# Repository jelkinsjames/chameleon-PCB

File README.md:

# University of Washington Engine Chameleon Team 2023
This repo documents the University of Washington ENGINE 2023 Chameleon Team's journey towards creating a digital, modular synthesizer - a **Chameleon**. The team consists of Todd Bloom, Max Chastain, Nathan Ford, Julian James, and Trina Kha. The mentor for the project is Eric Klavins.

Each individual component of the project has its own README.md file. The instructional files are:
- [PCM1863 ADC](https://github.com/jelkinsjames/chameleon-PCB/tree/main/PCM1863/README.md)
- [PCM5242 DAC](https://github.com/jelkinsjames/chameleon-PCB/blob/main/PCM5242/README.md)

Eric Klavins hosts GitHub repos with the software used for the project. The software is Yet Another Synthesizer Engine (YASE). Links to relevant repos are provided below:
- [yase](https://github.com/klavins/yase.git): The synthesizer engine used in the project.
- [yase-template](https://github.com/klavins/yase-template.git): The template .makefile to be used when installing YASE.
- [potato-recipies](https://github.com/klavins/potato-recipies.git): Instructions on how to install and use YASE on Le Potato (an alternate board similar to a Raspberry Pi).
- [arty-z7-20-recipies](https://github.com/klavins/arty-z7-20-recipes.git): Instructions on how to install and use YASE on an ARTY-Z7-20 (an alternate board similar to a Raspberry Pi).

## Project Overview:

The Chameleon can function as a waveform generator, filter, effect, sequencer, and any other programmable module.

The **user interface** includes: *four LEDs, four rotary encoders, and four toggle switches.*

The **inputs** are: *Two stereo S/PDIF inputs* to take incoming data from other Chameleons and *two line-level mono-analog audio inputs.*

The **outputs** are: *Four stereo S/PDIF outputs* (carrying the same signal) that can be connected to other Chameleons and *two line-level mono-analog audio outputs.*

---

## Block Diagram:

### ARTY-Z7:
- [Xilinx Zynq 7020 SoC Processor](https://digilent.com/shop/arty-z7-zynq-7000-soc-development-board/)
- 650 MHz Dual core ARM processor
- 85,000 cell FPGA
- [Xilinx I2S FPGA module](https://www.xilinx.com/products/intellectual-property/audio-i2s.html)
- Four stereo channels that can be input or output
- 24-bit data at a frequency to be determined
- We are not sure if two I2S modules can be implemented. If so, we can have more I/O

The Chameleon Module sits on top of the ARTY board, which has female pin headers in the shape of an Arduino shield.

### Digital Inputs and Outputs (I/O):
- Each S/PDIF signal is stereo
- Inter-Chameleon connections are stereo
- You can’t split them into two mono signals from separate Chameleons.
- Digital I/O is managed by multiple DIX4192s
- Although there are four DINs, only one can be used at a time.
- There are two I2S lines, both can be either input or output

### Analog Inputs and Outputs (I/O):
- Analog input is managed by a [PCM1863 ADC](https://www.ti.com/product/PCM1863)
- Analog output is managed by a [PCM5242 DAC](https://www.ti.com/product/PCM5242)

### Front Panel and Skins:
- Front panel is black PCB with holes for UI elements
- PCB silkscreen is used for graphics
- The front panel fits in standard [Euroracks](https://en.wikipedia.org/wiki/Eurorack)
- Laser cut "skins" can be swapped out to match current Chameleon functionality

---

## User Interface (U/I):
- The UI is managed by an [ATSAMD21](https://www.microchip.com/en-us/product/ATsamd21g18) microcontroller
- The UI has four rotary encoders, LEDs, and toggle switches
- A custom I2C protocol is used to: *query the state of encoders and switches, reset encoders, and set LEDs.*

**The I2C Protocol is Register Based:**
- Each LED and switch correspond to a single bit in a single-byte-sized register
- Each encoder has a reset bit in a half-byte-sized reset register. Setting the corresponding bit high will reset the encoder's position
- Each encoder has a position register that can be read. When read, the register gives the position of the encoder in the range [0,255].

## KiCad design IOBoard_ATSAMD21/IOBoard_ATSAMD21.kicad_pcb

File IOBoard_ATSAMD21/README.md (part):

# I/O Board - ATSAMD21G18-A

---

This repository contains the hardware and software components of the I/O board for the Chameleon project.
The goal for this portion of the project is to create a peripheral to control [YASE](https://github.com/klavins/YASE). It can interface with any CPU using the I2C bus, and will allow users to modify parameters in YASE. The I/O board has rotary encoders, switches, and LEDs that the user can configure using I2C commands.

---
- [Hardware](#Hardware)

  - [Rotary Encoders](#Rotary-Encoders)
  - [Microcontrollers](#Microcontrollers)
  - [PCB Design](#PCB-Design)
  - [Analog Inputs and Outputs](#Analog-Inputs-and-Outputs)
  - [Programming/Debugging](#Programming-and-Debugging)

- [Software](#Software)
  - [Sercom I2C Functionality](#Sercom-I2C-Functionality)
  - [Talking to the IO Board](#Talking-to-the-IO-Board)

---
## Hardware

### Rotary Encoders
To allow users to modify YASE parameters with a knob, we are using rotary encoders. While rotary encoders may appear visually similar to a potentiometer you may find on a guitar or analog synthesizer module, they are fundamentally different. Instead of behaving like a variable resistor, rotary encoders are more similar to a rotary, dual-pole, dual-throw switch. Rotary encoders also spin indefinitely and do not have a start and end like a potentiometer.

The [How To Mechatronics](https://howtomechatronics.com/tutorials/arduino/rotary-encoder-works-use-arduino/) website has a great tutorial and explanation for how rotary encoders work.

A rotary encoder has 3 pins. The middle pin (C) is a shared power pin, which is connected to a power source. As the encoder spins, a brush powered by the middle pin makes contact with the left (A) and right (B) pins in sequence.

Since A and B are sent high at slightly different times, we can determine the direction of spin by measuring the state of A and B when a change in one is detected. This task is surprisingly simple to code.
Initially, we sample the value of `A` as value `aLast`. In a loop, we check to see if `aLast == A`. If `A != aLast`, we check the value of `B`. If `B == A`, we know `B` changed before `A` and the knob has been turned to the left. If `B != A`, then we know `A` changed first and the knob was turned to the right. Sample C code for managing one encoder is shown below.

```C
uint8_t encVal = 0;
_Bool aLast = A;
while(1) {
  if (A != aLast) {
    if(A != B) {
      encVal++;
    } else {
      encVal--;
    }
  }
  aLast = A;
}
```

I chose to use the PEC12R-3217F-S0024-ND rotary encoders because other similar projects used them. They include an extra switch that goes high when you press down on the knob. As an added bonus, they make a very satisfying clicking sound when pressed.

### Microcontrollers

The state of the encoders, LEDs, and switches are managed by a microprocessor. Initially I prototyped using the Arduino UNO, due its ease of use. However, the ATMEGA328P microcontroller it uses does not have enough GPIO to support the amount of peripherals we decided to use.

We have 4 rotary encoders, 4 switches, and 4 LEDs. Each encoder uses 3 GPIO (2 for the encoder and one for the pushbutton switch). Each switch and LED uses one GPIO. On top of this, I need two pins for accessing the I2C bus. This totals 22 GPIO. I could have used two microcontrollers, however choosing one that has enough GPIO to begin with seemed like a smarter idea so that I wouldn't have to write two separate programs.

This GPIO requirement led me to the ATSAMD21G18, an ARM-based microcontroller used on the Arduino Zero. This microprocessor is honestly way more powerful than we will take advantage of, but they are relatively cheap, widely available, and have more than enough GPIO. This will allow expansion in the future if a different team decides they want to add something else!

### PCB Design

The biggest design consideration made for the PCB was making it compatible with other Eurorack modules. Eurorack modules have the following size constraints:
- Height - 128.5mm/5.06"
- Width - in increments of 0.2", called a Horizontal Pitch (HP)
- Mounting holes - 3.2mm diameter
- Left mounting holes aligned 3mm from top and bottom edge, and 7.45mm from the left edge
- Right mounting holes aligned in HP increments from the left holes

For the IO board, I chose a width of 15HP. I found this size to be a good width for fitting all the components we needed. Since the I/O board will be sitting underneath the front panel, I reduced the overall dimension by 16.5mm. This allows the board to fit nicely inside a Eurorack style skiff.

I placed the rotary encoders, LEDs, and switches on a grid of 0.1" so that I could make them symmetrical across the middle of the board. I used a smaller grid for the ATSAMD21G18 and bypass capacitors to make routing easier. The ATSAMD21G18 has both internal pull up and pull down resistors, so there was no need to include extra resistors on the board, except for the resistors used for the LEDs. I found 10k ohms to yield a good brightness for the LEDs in testing.

For power, I am using a 3.3v LDO. I chose this instead of stealing power from the main computer in hopes that it may be a little more stable and allow for expansion in the future.

Next to every power pin on the SAMD21, I included two bypass capacitors. I chose 0.1uF and 10uF capacitors as it is typically recommended the larger bypass capacitor are 100x the smaller's capacitance. Ideally, I would have used both a tantalum and a ceramic capacitor for better performance, but as this board is purely digital I am not overly concerned with noise. Ceramic capacitors are not polar, so it is a little easier to assemble the boards using both ceramic.

All capacitors and resistors use the 0603 package for consistency.

The entire back copper layer of my PCB is a ground plane. This makes it very easy to ground anything that I need by placing a via. Once all of my components were connected to the ATSAMD21G18, I made the rest of the front copper layer a +3.3v power plane. This meant I did not have to route any power traces on the board, vastly simplifying the amount of time it took to design the PCB.

The switches are single throw, dual pole. This choice was made largely because they are much cheaper than single throw, single pole switches and readily available. I connected the middle pin to power, and the top pin to the SAM's GPIO.

### Analog Inputs and Outputs

In the final version of this board, I added 6 mono-analog jacks to the bottom half of the board. The left four are inputs, designed to go to the ADC. There are dedicated switches to choose which of the inputs you are using. The leftmost two are for control voltage (CV) and the middle two are for line level (LL). CV typically ranges from 0-10V, while LL ranges from 0-1V. Because of these vastly different voltage ranges, these inputs are buffered using an op-amp to prevent damage to the ADC board. The two rightmost jacks are dedicated to DAC out. These include an op-amp pre-amplification stage for lower signal-to-noise ratio.

The DAC output and ADC input pins are located on the rear of the I/O board, and are designed to be connected to the DAC and ADC peripherals designed by my teammates.

**These inputs will do nothing without an ADC or DAC. They do not interface with the D21.**

### Programming and Debugging

I use the Microchip PICkit4 to debug/program the SAMD21. I used the recommended debug header provided by KiCad 6. While this seemed to be easy initially, I realized that there was no easily accessible documentation as to what the PICkit4's 8 pins do! Different resources were saying different things, so it required a little guess and check work. To make matters worse, for some silly reason pin 1 of the PICkit4 is the furthest **RIGHT** instead of furthest left like every other convention you might be used to. The only clue I had to this was the arrow pointing at that pin.

To make things much easier for you, here is a list of the PICkit4 pins and where to plug them into the IO Board (from right to left)

1. MCLR
2. VDD
3. GND
4. Not connected
5. SWCLK
6. Not connected  
7. Not connected
8. SWDIO

The recommended header I used on my PCB has this in the same order and are labeled clearly, this should be very straight forward. Once plugged into the powered board, MPLAB will automatically recognize that it has a valid device to program. You may need to select the PICkit4 as your debugger in the IDE somewhere if this does not work automatically.

---

## Software

Programming the ATSAMD21G18 is fairly straight forward (with a few exceptions mostly due to Microchip's bad documentation). I am using the PICkit4 debugger to program the SAM. To write the code, I initially thought I may be able to use the Arduino IDE. This which would vastly simplify the programming, and may still be possible. The Arduino IDE supports the SAMD21, however it does not have support for the PICkit4. It supports the Atmel ICE debugger, which no longer exists since Microchip bought Atmel and now uses the PICkit4 as it's preferred debugger even though the ATSAM family of chips were originally produced by Atmel. *Can you tell I'm annoyed about this?*

I'm sure it is possible to trick the Arduino IDE into thinking that the PICkit4 is an Atmel ICE, but I do not know how to do that.

Instead, I am using Microchip's [MPLAB X IDE](https://www.microchip.com/mplab) to program my SAMD21. In true Microchip fashion, this turned out to be way more work than I wanted it to be! My goal was to use the Harmony3 tool to assist with configuring the chip. This is supposed to be installed by default, but for some reason it was not.

I had to clone the [GitHub repository for the MPLAB Harmony Content Manager](https://github.com/Microchip-MPLAB-Harmony/contentmanager), run it from the terminal, and use that to install the required packages for Harmony3. Once all of that was finished, I was finally able to use Harmony to write most of the code I needed. While this certainly saved me from reading the datasheet for hours and hours to learn how to program the chip, it led to the problem of me not understanding how the code worked at all!

### SERCOM I2C Functionality
My first big mistake was not enabling smart mode for the SERCOM I2C module inside Harmony3. Smart mode automates most of the I2C transactions, which greatly simplifies the coding. Before I realized that I should be using smart mode, I ran into a very strange issue with the address match interrupt. The code generate by Harmony3 included an interrupt manager. For whatever reason, the interrupt manager would not reset the address match interrupt and instead would get stuck in a time-out state. It took me weeks to figure out what was going on, and in the end it just took me turning smart mode on and Harmony rewrote the interrupt manager to deal with the issue I was having.

Once smart mode was enabled, all that is left to do is write a callback function for the SERCOM I2C module. Using a switch statement allows you to choose desired behavior when certain events take place. For my code, I only care about receiving and sending data, and do not care about doing anything specific on address match or on an error. A basic form of this callback function is shown below.

```C
uint8_t rxReg;
uint8_t txReg;
bool I2C_Callback(SERCOM_I2C_SLAVE_TRANSFER_EVENT event, uintptr_t contextHandle) {
    switch(event) {
      case SERCOM_I2C_SLAVE_TRANSFER_EVENT_RX_READY:
          rxReg = SERCOM0_I2C_ReadByte();
          // You can execute any code you want here, I use another switch statement
          switch(rxReg) {
            case 0x00:
              ENC0_val = 0;
              txReg = ENC0_val;
              break;

            case 0x01:
              txReg = ENC0_val;
              break;                
          }
        break;

      case SERCOM_I2C_SLAVE_TRANSFER_EVENT_TX_READY:
          SERCOM0_I2C_WriteByte(txReg);
          txReg = 0;
        break;
    }
    return true;
}
```

For this project, we will always read a value before writing a value. The value we write is determined by the value previously read. Because of this, I fill `txReg` with the correct data based on what we read from the I2C host. For example, if the host wishes to read the value of `ENC0`, it will first write `0x01` to `rxReg`. We next check the value of `rxReg` and enter the correct case statement. As shown above we just fill `txReg` with `ENC0_val`.

Once this host write operation has finished, the host will initiate a read operation. The I/O Board will respond with the contents of `txReg` and then reset the value to 0. My callback function always returns `true`. If you return false instead, the I2C acknowledgement bit will not be set high. This can be useful to tell the host that data is not ready for transmission. For my application there are no cases in which we won't send valid data, so I always return `true`.

The events you can add to your callback function are as follows:
- `SERCOM_I2C_SLAVE_TRANSFER_EVENT_RX_READY`
- `SERCOM_I2C_SLAVE_TRANSFER_EVENT_TX_READY`
- `SERCOM_I2C_SLAVE_TRANSFER_EVENT_ADDR_MATCH`
- `SERCOM_I2C_SLAVE_TRANSFER_EVENT_STOP_BIT_RECEIVED`
- `SERCOM_I2C_SLAVE_TRANSFER_EVENT_ERROR`

Now that we have a completed callback function, we just need to tell the SERCOM module to use this function by calling `SERCOM0_I2C_CallbackRegister(I2C_Callback, 0)` in our main function.

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
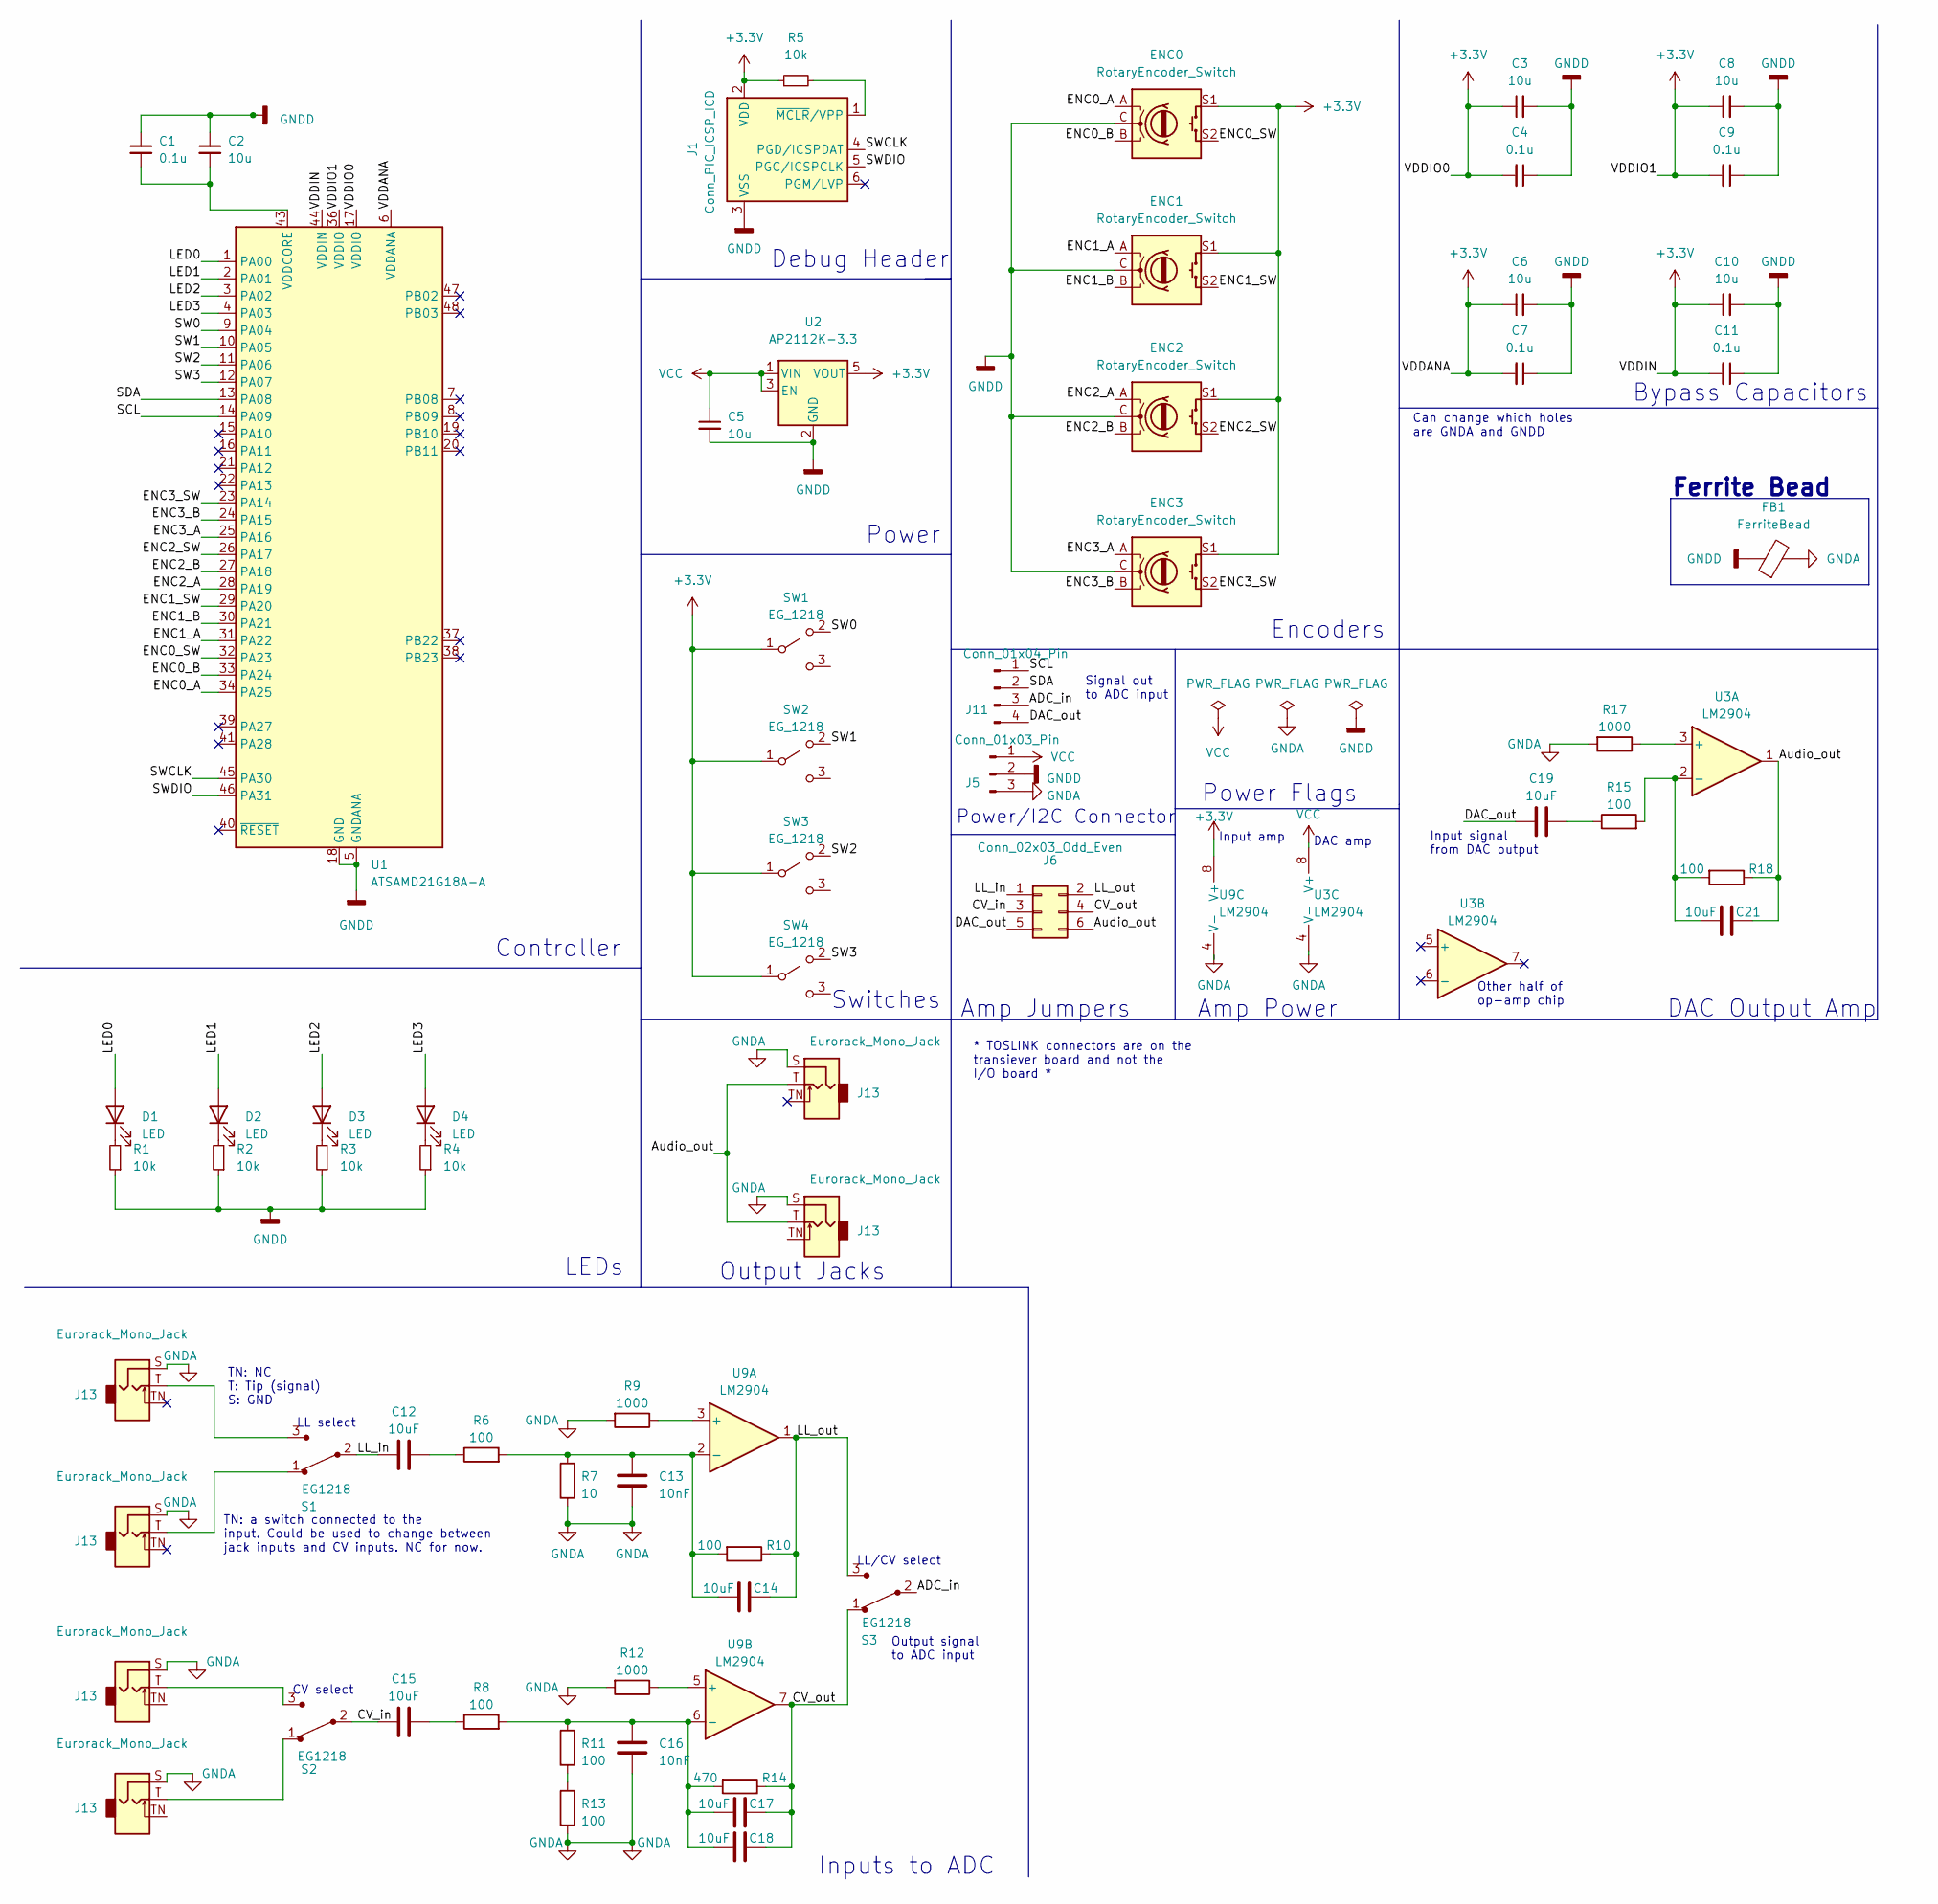
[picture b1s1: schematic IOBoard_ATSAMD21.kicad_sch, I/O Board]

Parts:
C1, C4, C7, C9, C11: 0.1u; C_0603_1608Metric
C2, C3, C5, C6, C8, C10: 10u; C_0603_1608Metric
C12, C14, C15, C17, C18, C19, C21: 10uF; C_0603_1608Metric
C13, C16: 10nF; C_0603_1608Metric
D1, D2, D3, D4: LED; LED_Rectangular_W5.0mm_H2.0mm
ENC0, ENC1, ENC2, ENC3: RotaryEncoder_Switch; PEC12R-3217F-S0024-ND
FB1: FerriteBead; L_0603_1608Metric_Pad1.05x0.95mm_HandSolder
J1: Conn_PIC_ICSP_ICD; PinHeader_1x06_P2.54mm_Vertical
J5: Conn_01x03_Pin; PinHeader_1x03_P2.54mm_Vertical
J6: Conn_02x03_Odd_Even; PinHeader_2x03_P2.54mm_Vertical
J11: Conn_01x04_Pin; PinHeader_1x04_P2.54mm_Vertical
J13: Eurorack_Mono_Jack; AudioJack_WQP518MA; MPN WQP-WQP518MA
R1, R2, R3, R4, R5: 10k; R_0603_1608Metric
R6, R8, R10, R11, R13, R15, R18: 100; R_0603_1608Metric
R7: 10; R_0603_1608Metric
R9, R12, R17: 1000; R_0603_1608Metric
R14: 470; R_0603_1608Metric
S1, S2, S3: EG1218; EG_1218; MPN EG1218; Digi-Key_PN EG1903-ND
SW1, SW2, SW3, SW4: EG_1218
U1: ATSAMD21G18A-A; TQFP-48_7x7mm_P0.5mm
U2: AP2112K-3.3; SOT-23-5
U3, U9: LM2904; SOIC-8_3.9x4.9mm_P1.27mm

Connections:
+3.3V: C3.1, C4.2, C6.1, C7.2, C8.1, C9.2, C10.1, C11.2, ENC0.S1, ENC1.S1, ENC2.S1, ENC3.S1, J1.2 (VDD), R5.1, SW1.1, SW2.1, SW3.1, SW4.1, U1.6 (VDDANA), U1.17 (VDDIO), U1.36 (VDDIO), U1.44 (VDDIN), U2.5 (VOUT), U9.8 (V+)
/ADC_in: J11.3, S3.2
/Audio_out: C21.1, J6.6, R18.1, U3.1; also elsewhere on the board
/CV_in: C15.1, J6.3, S2.2
/CV_out: C17.1, C18.1, J6.4, R14.1, S3.1, U9.7
/DAC_out: C19.1, J6.5, J11.4
/ENC0_A: ENC0.A, U1.34 (PA25)
/ENC0_B: ENC0.B, U1.33 (PA24)
/ENC0_SW: ENC0.S2, U1.32 (PA23)
/ENC1_A: ENC1.A, U1.31 (PA22)
/ENC1_B: ENC1.B, U1.30 (PA21)
/ENC1_SW: ENC1.S2, U1.29 (PA20)
/ENC2_A: ENC2.A, U1.28 (PA19)
/ENC2_B: ENC2.B, U1.27 (PA18)
/ENC2_SW: ENC2.S2, U1.26 (PA17)
/ENC3_A: ENC3.A, U1.25 (PA16)
/ENC3_B: ENC3.B, U1.24 (PA15)
/ENC3_SW: ENC3.S2, U1.23 (PA14)
/LED0: D1.2 (A), U1.1 (PA00)
/LED1: D2.2 (A), U1.2 (PA01)
/LED2: D3.2 (A), U1.3 (PA02)
/LED3: D4.2 (A), U1.4 (PA03)
/LL_in: C12.1, J6.1, S1.2
/LL_out: C14.1, J6.2, R10.1, S3.3, U9.1
/SCL: J11.1, U1.14 (PA09)
/SDA: J11.2, U1.13 (PA08)
/SW0: SW1.2, U1.9 (PA04)
/SW1: SW2.2, U1.10 (PA05)
/SW2: SW3.2, U1.11 (PA06)
/SW3: SW4.2, U1.12 (PA07)
/SWCLK: J1.4 (PGD/ICSPDAT), U1.45 (PA30)
/SWDIO: J1.5 (PGC/ICSPCLK), U1.46 (PA31)
GNDA: C13.1, C16.1, FB1.2, J5.3, R7.1, R9.2, R12.2, R13.1, R17.2, U3.4 (V-), U9.4 (V-); also elsewhere on the board
GNDD: C1.1, C2.1, C3.2, C4.1, C5.2, C6.2, C7.1, C8.2, C9.1, C10.2, C11.1, ENC0.C, ENC1.C, ENC2.C, ENC3.C, FB1.1, J1.3 (VSS), J5.2, R1.1, R2.1, R3.1, R4.1, U1.5 (GNDANA), U1.18 (GND), U1.35 (GND), U1.42 (GND), U2.2 (GND)
unnamed: C12.2, R6.1
unnamed: C15.2, R8.1
unnamed: C19.2, R15.1
unnamed: D1.1 (K), R1.2
unnamed: D2.1 (K), R2.2
unnamed: D3.1 (K), R3.2
unnamed: D4.1 (K), R4.2
unnamed: J1.1 (~MCLR/VPP), R5.2
unnamed 42: S1.3; also elsewhere on the board
unnamed 43: S1.1; also elsewhere on the board
unnamed 44: S2.3; also elsewhere on the board
unnamed 45: S2.1; also elsewhere on the board
unnamed: R11.1, R13.2
unnamed: C1.2, C2.2, U1.43 (VDDCORE)
unnamed: R17.1, U3.3 (+)
unnamed: C21.2, R15.2, R18.2, U3.2 (-)
unnamed: R9.1, U9.3 (+)
unnamed: C13.2, C14.2, R6.2, R7.2, R10.2, U9.2 (-)
unnamed: R12.1, U9.5 (+)
unnamed: C16.2, C17.2, C18.2, R8.2, R11.2, R14.2, U9.6 (-)
VCC: C5.1, J5.1, U2.1 (VIN), U2.3 (EN), U3.8 (V+)

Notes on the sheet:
LL/CV select
TN: NC T: Tip (signal) S: GND
Input signal from DAC output
Other half of op-amp chip
CV select
LEDs
DAC amp
DAC Output Amp
Debug Header
Encoders
Amp Jumpers
Output Jacks
Switches
Ferrite Bead
Power
Input amp
* TOSLINK connectors are on the transiever board and not the I/O board *
Amp Power
Inputs to ADC
Power/I2C Connector
Signal out to ADC input
TN: a switch connected to the input. Could be used to change between jack inputs and CV inputs. NC for now.
Controller
LL select
Bypass Capacitors
Can change which holes are GNDA and GNDD
Power Flags
Output signal to ADC input

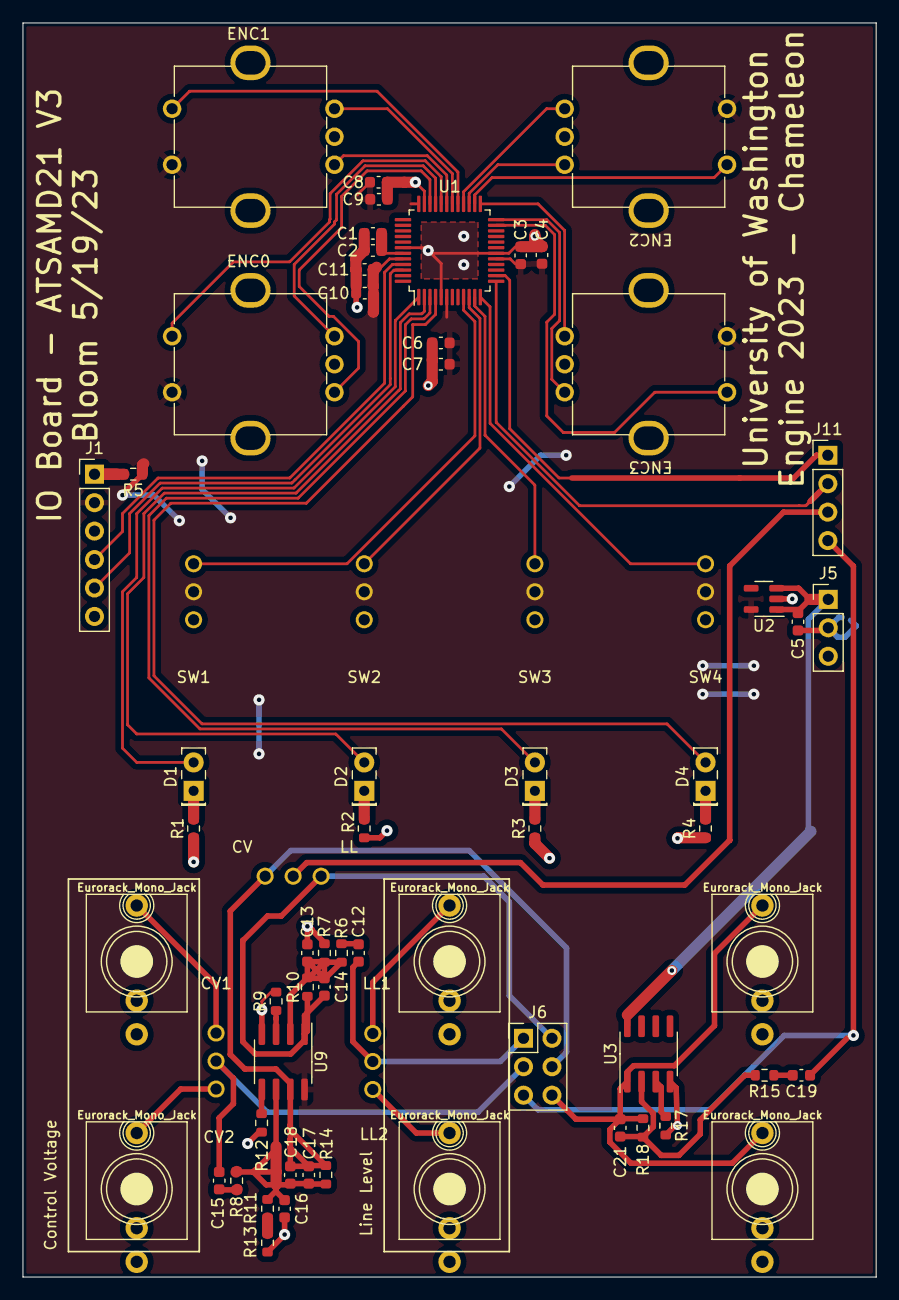
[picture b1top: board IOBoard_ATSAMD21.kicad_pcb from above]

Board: 2 copper layers, 76.2 x 112.0 mm, 67 parts (1 on the bottom side), 55 nets.

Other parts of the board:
J2, J3, J4, J7, J8, J10: Eurorack_Mono_Jack; AudioJack_WQP518MA

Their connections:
/Audio_out: J2.T (Tip), J10.T (Tip); also elsewhere on the board
GNDA: J2.S (Sleeve), J3.S (Sleeve), J4.S (Sleeve), J7.S (Sleeve), J8.S (Sleeve), J10.S (Sleeve); also elsewhere on the board
unnamed 42: J3.T (Tip); also elsewhere on the board
unnamed 43: J4.T (Tip); also elsewhere on the board
unnamed 44: J7.T (Tip); also elsewhere on the board
unnamed 45: J8.T (Tip); also elsewhere on the board

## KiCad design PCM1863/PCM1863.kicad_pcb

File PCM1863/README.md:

# PCM1863 ADC

The purpose of the ADC in the system is to take analog inputs from control voltages (5V) and convert them into readable I2S digital signals. The digital signals will be processed by the embedded board to be modified by [YASE](https://github.com/klavins/yase) (a synthesizer engine created by Eric Klavins).

The ADC creation has three steps:
1. [Creating the physical ADC board](https://github.com/jelkinsjames/chameleon-PCB/tree/main/PCM1863/board)
2. [Setting up the ADC board and embedded board](https://github.com/jelkinsjames/chameleon-PCB/tree/main/PCM1863/setup)
3. [Using the ADC with the embedded board](https://github.com/jelkinsjames/chameleon-PCB/tree/main/PCM1863/usage)

We will be using the PCM1863 chip by TI for our ADC. The [PCM1863](https://www.ti.com/product/PCM1863?utm_source=google&utm_medium=cpc&utm_campaign=asc-null-null-GPN_EN-cpc-pf-google-wwe&utm_content=PCM1863&ds_k=PCM1863&DCM=yes&gclid=Cj0KCQiA6fafBhC1ARIsAIJjL8l6Lk9SO-Q0-fB0_5uYiveTayMeogbHzMJUxCBsQcNd4n_-5XY2ie4aAl2cEALw_wcB&gclsrc=aw.ds) is an audio-controlled analog-to-digital (ADC) converter. The chip is 110dB 2-channel software controlled. The chip is made by Texas Instruments (TI), and its datasheet is available here: [PCM1863 Datasheet](https://www.ti.com/lit/ds/symlink/pcm1861-q1.pdf?HQS=dis-dk-null-digikeymode-dsf-pf-null-wwe&ts=1676585219889&ref_url=https%253A%252F%252Fwww.ti.com%252Fgeneral%252Fdocs%252Fsuppproductinfo.tsp%253FdistId%253D10%2526gotoUrl%253Dhttps%253A%252F%252Fwww.ti.com%252Flit%252Fgpn%252Fpcm1861-q1). The chip is a TSSOP (DBT) 30 pin package. The chip is hardware and software controllable.

Drivers for the PCM 186x series are available [here](https://e2e.ti.com/support/audio-group/audio/f/audio-forum/773056/faq-linux-drivers-device-drivers-for-aic31xx-dac31xx-aic325x-aic320x-aic326x-aic321x). More driver information can be found on the [TI webpage](https://www.ti.com/product/PCM1863?utm_source=google&utm_medium=cpc&utm_campaign=asc-null-null-GPN_EN-cpc-pf-google-wwe&utm_content=PCM1863&ds_k=PCM1863&DCM=yes&gclid=Cj0KCQiA6fafBhC1ARIsAIJjL8l6Lk9SO-Q0-fB0_5uYiveTayMeogbHzMJUxCBsQcNd4n_-5XY2ie4aAl2cEALw_wcB&gclsrc=aw.ds) for the PCM1863.

The [Ti PCM186X Evaluation Board](https://www.ti.com/lit/ug/slau615/slau615.pdf?ts=1678288360067&ref_url=https%253A%252F%252Fwww.ti.com%252Fproduct%252FPCM1864) has additional resources on how to design an example board. [PurePath Console 3 (PPC3)](https://www.ti.com/tool/PUREPATHCONSOLE) is a GUI for development of audio chips such as the PCM1863

Here is a block diagram of the chip we are using:

---

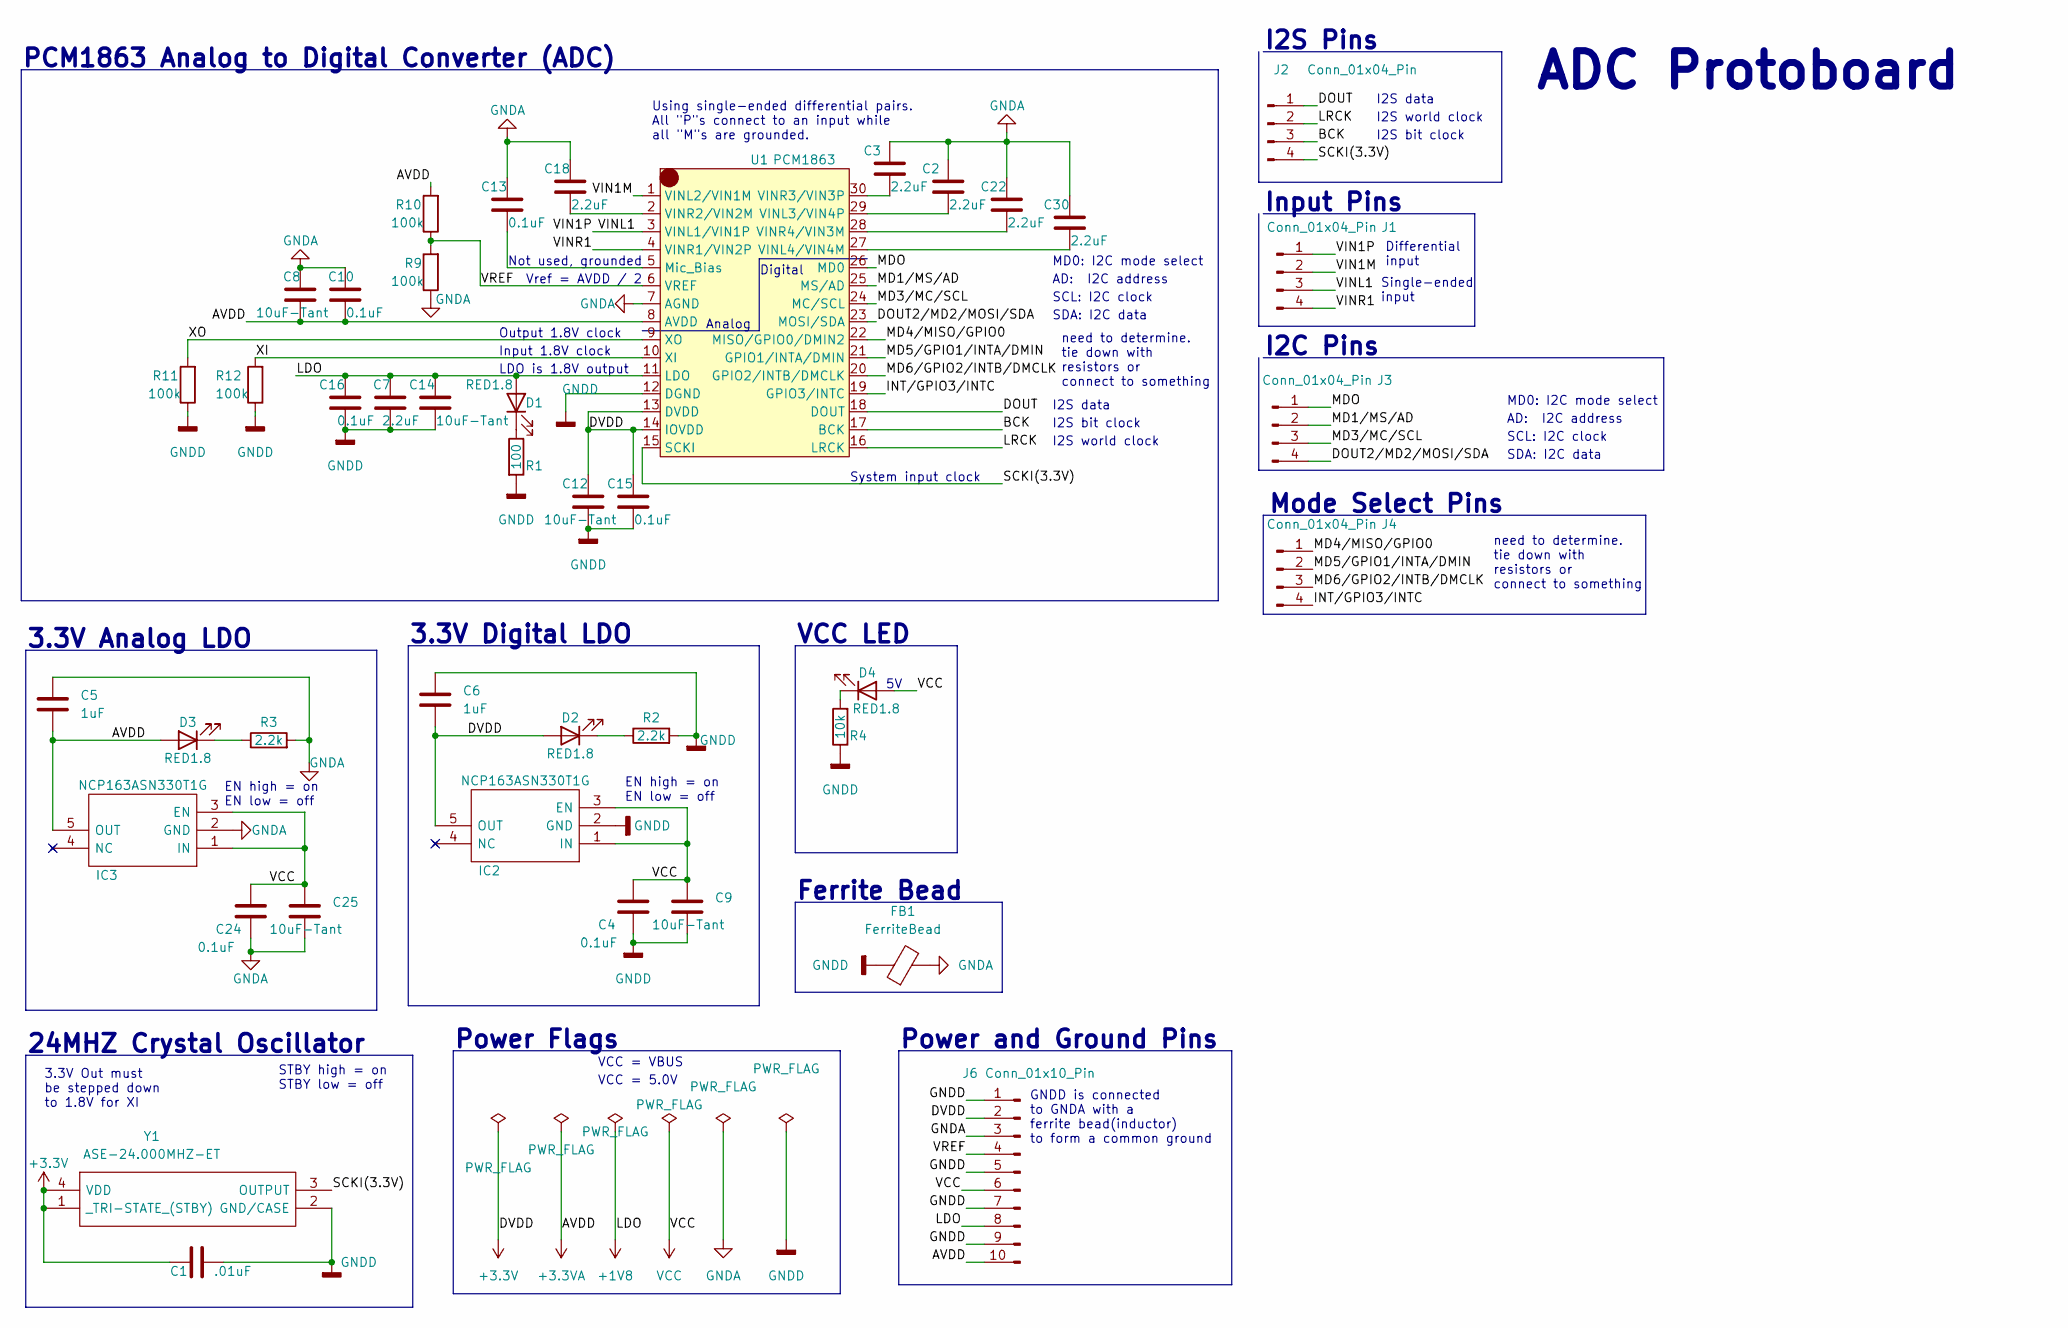
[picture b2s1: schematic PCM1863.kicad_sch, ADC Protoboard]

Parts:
C1: .01uF; C_0603_1608Metric_Pad1.08x0.95mm_HandSolder
C2, C3, C7, C18, C22, C30: 2.2uF; C_0603_1608Metric_Pad1.08x0.95mm_HandSolder
C4, C10, C13, C15, C16, C24: 0.1uF; C_0603_1608Metric_Pad1.08x0.95mm_HandSolder
C5, C6: 1uF; C_0603_1608Metric_Pad1.08x0.95mm_HandSolder
C8, C9, C12, C14, C25: 10uF-Tant; C_0603_1608Metric_Pad1.08x0.95mm_HandSolder
D1, D2, D3, D4: RED1.8; LED_0603_1608Metric_Pad1.05x0.95mm_HandSolder
FB1: FerriteBead; L_0603_1608Metric_Pad1.05x0.95mm_HandSolder
IC2, IC3: NCP163ASN330T1G; SOT95P280X145-5N; Manufacturer_Part_Number NCP163ASN330T1G; Mouser Part Number 863-NCP163ASN330T1G
J1, J2, J3, J4: Conn_01x04_Pin; PinHeader_1x04_P2.54mm_Vertical
J6: Conn_01x10_Pin; PinHeader_1x10_P2.54mm_Vertical
R1: 100; R_0603_1608Metric_Pad0.98x0.95mm_HandSolder
R2, R3: 2.2k; R_0603_1608Metric_Pad0.98x0.95mm_HandSolder
R4: 10k; R_0603_1608Metric_Pad0.98x0.95mm_HandSolder
R9, R10, R11, R12: 100k; R_0603_1608Metric_Pad0.98x0.95mm_HandSolder
U1: PCM1863; TSSOP-30_4.4x7.8mm_P0.5mm
Y1: ASE-24.000MHZ-ET; ASE24000MHZET; Manufacturer_Part_Number ASE-24.000MHZ-ET; Mouser Part Number 815-ASE24.000MHZET

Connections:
+1V8: C7.1, C14.1, C16.1, D1.2 (A), J6.8, U1.11 (LDO)
+3.3VA: C5.2, C8.2, C10.2, D3.2 (A), IC3.5 (OUT), J6.10, R10.2, U1.8 (AVDD)
+3V3: C1.1, C6.2, C12.1, C15.1, D2.2 (A), IC2.5 (OUT), J6.2, U1.13 (DVDD), U1.14 (IOVDD), Y1.1 (_TRI-STATE_(STBY)), Y1.4 (VDD)
/BCK: J2.3, U1.17 (BCK)
/DOUT: J2.1, U1.18 (DOUT)
/DOUT2/MD2/MOSI/SDA: J3.4, U1.23 (MOSI/SDA)
/INT/GPIO3/INTC: J4.4, U1.19 (GPIO3/INTC)
/LRCK: J2.2, U1.16 (LRCK)
/MD1/MS/AD: J3.2, U1.25 (MS/AD)
/MD3/MC/SCL: J3.3, U1.24 (MC/SCL)
/MD4/MISO/GPIO0: J4.1, U1.22 (MISO/GPIO0/DMIN2)
/MD5/GPIO1/INTA/DMIN: J4.2, U1.21 (GPIO1/INTA/DMIN)
/MD6/GPIO2/INTB/DMCLK: J4.3, U1.20 (GPIO2/INTB/DMCLK)
/MDO: J3.1, U1.26 (MD0)
/SCKI(3.3V): J2.4, U1.15 (SCKI), Y1.3 (OUTPUT)
/VIN1M: J1.2, U1.1 (VINL2/VIN1M)
/VIN1P: J1.1, J1.3, U1.3 (VINL1/VIN1P)
/VINR1: J1.4, U1.4 (VINR1/VIN2P)
/VREF: J6.4, R9.2, R10.1, U1.6 (VREF)
/XI: R12.2, U1.10 (XI)
/XO: R11.2, U1.9 (XO)
GNDA: C2.1, C3.1, C5.1, C8.1, C10.1, C13.1, C18.1, C22.1, C24.2, C25.2, C30.1, FB1.2, IC3.2 (GND), J6.3, R3.2, R9.1, U1.7 (AGND)
GNDD: C1.2, C4.2, C6.1, C7.2, C9.2, C12.2, C14.2, C15.2, C16.2, FB1.1, IC2.2 (GND), J6.1, J6.5, J6.7, J6.9, R1.2, R2.2, R4.1, R11.1, R12.1, U1.12 (DGND), Y1.2 (GND/CASE)
unnamed: D1.1 (K), R1.1
unnamed: D2.1 (K), R2.1
unnamed: D3.1 (K), R3.1
unnamed: D4.1 (K), R4.2
unnamed: C13.2, U1.5 (Mic_Bias)
unnamed: C2.2, U1.29 (VINL3/VIN4P)
unnamed: C30.2, U1.27 (VINL4/VIN4M)
unnamed: C18.2, U1.2 (VINR2/VIN2M)
unnamed: C3.2, U1.30 (VINR3/VIN3P)
unnamed: C22.2, U1.28 (VINR4/VIN3M)
VCC: C4.1, C9.1, C24.1, C25.1, D4.2 (A), IC2.1 (IN), IC2.3 (EN), IC3.1 (IN), IC3.3 (EN), J6.6

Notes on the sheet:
Digital
I2S world clock
Output 1.8V clock
Vref = AVDD / 2
I2S data
MD0: I2C mode select
System input clock
need to determine. tie down with resistors or connect to something
I2C Pins
Power Flags
STBY high = on STBY low = off
SCL: I2C clock
I2S Pins
LDO is 1.8V output
GNDD is connected to GNDA with a ferrite bead(inductor) to form a common ground
I2S bit clock
EN high = on EN low = off
PCM1863 Analog to Digital Converter (ADC)
VCC LED
ADC Protoboard
SDA: I2C data
3.3V Analog LDO
3.3V Out must be stepped down to 1.8V for XI
Input 1.8V clock
3.3V Digital LDO
Single-ended input
Not used, grounded
VCC = VBUS
VCC = 5.0V
Ferrite Bead
AD: I2C address
Mode Select Pins
Input Pins
Power and Ground Pins
Differential input
24MHZ Crystal Oscillator
Analog
Using single-ended differential pairs. All "P"s connect to an input while all "M"s are grounded.

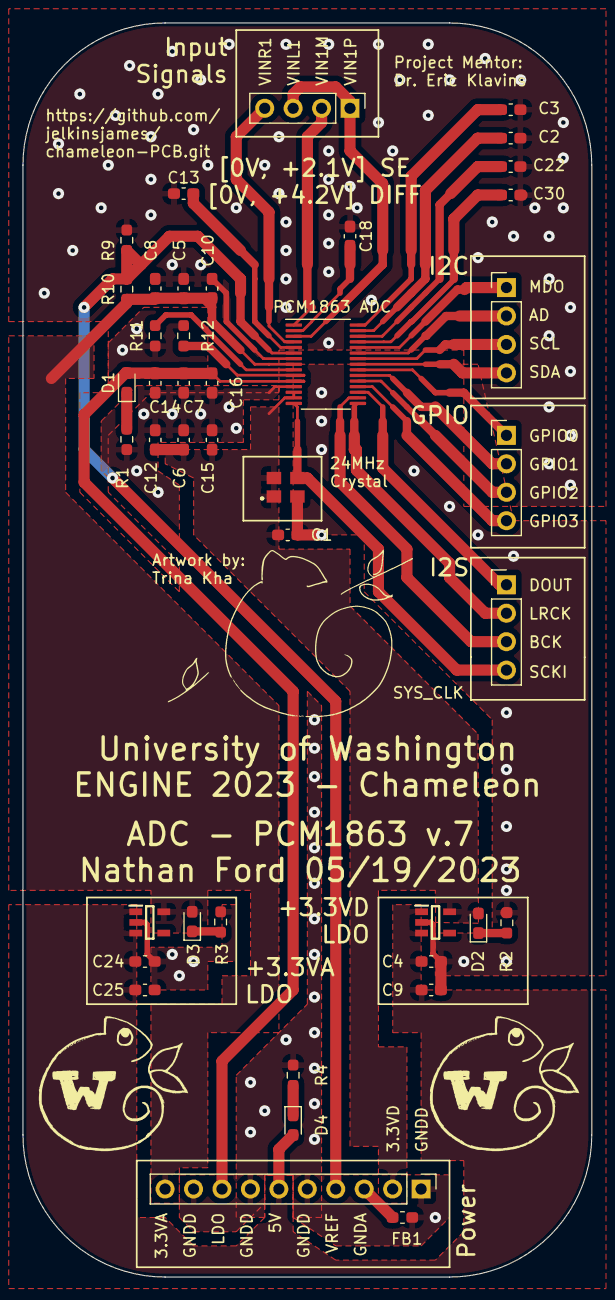
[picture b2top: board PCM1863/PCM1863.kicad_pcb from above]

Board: 2 copper layers, 50.8 x 112.0 mm, 42 parts (0 on the bottom side), 34 nets.

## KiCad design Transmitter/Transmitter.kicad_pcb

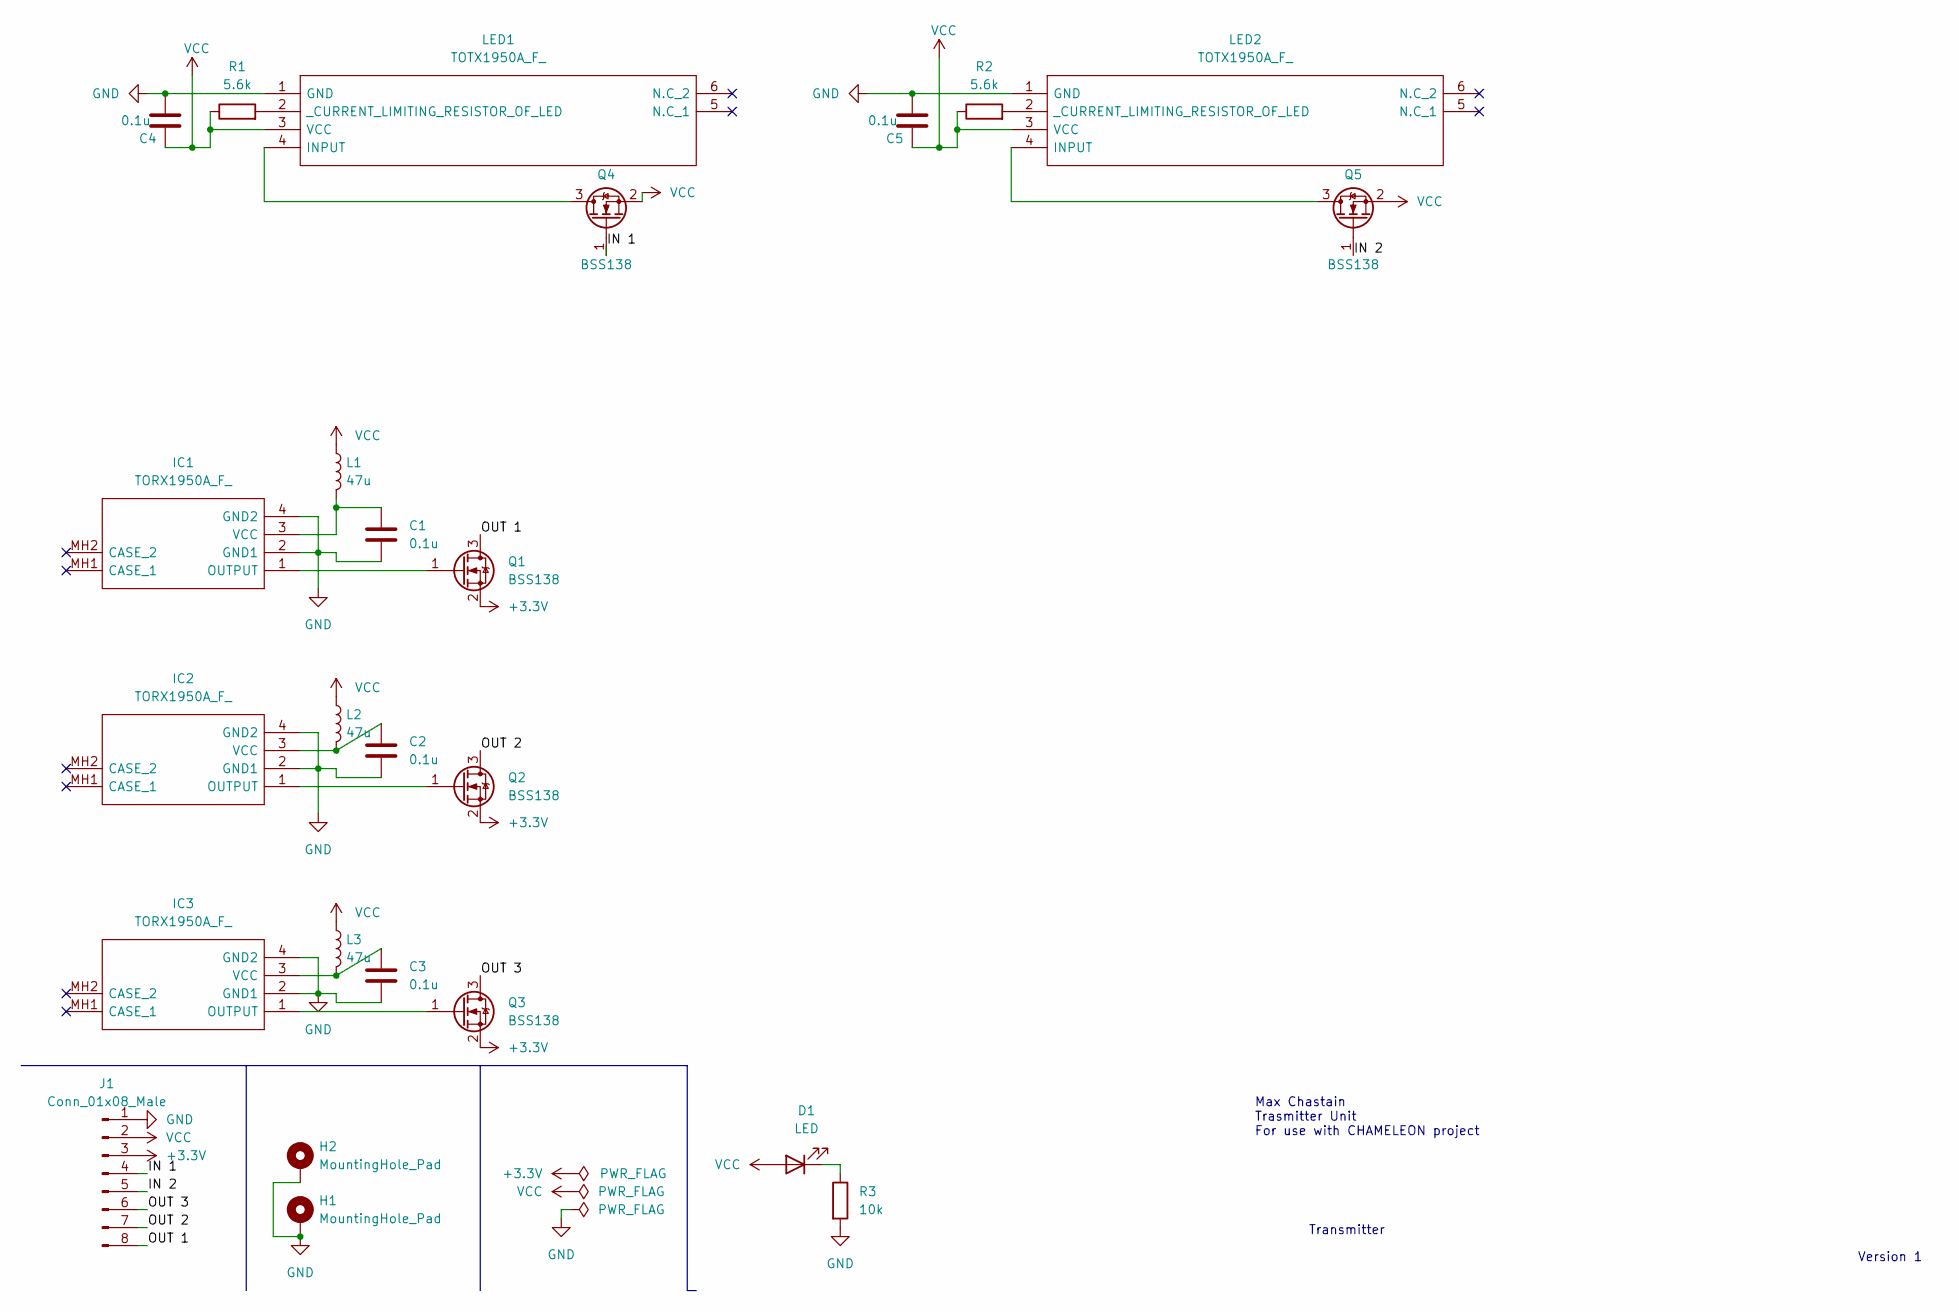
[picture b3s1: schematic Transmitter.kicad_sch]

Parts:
C1, C2, C3, C4, C5: 0.1u; C_0603_1608Metric_Pad1.08x0.95mm_HandSolder
D1: LED; LED_D8.0mm
H1, H2: MountingHole_Pad; MountingHole_3.2mm_M3_ISO7380_Pad
IC1, IC2, IC3: TORX1950A_F_; TORX1950AF; Mouser Part Number 71-TORX1950A(F)
J1: Conn_01x08_Male; PinHeader_1x08_P2.54mm_Vertical
L1, L2, L3: 47u; L_0603_1608Metric_Pad1.05x0.95mm_HandSolder
LED1, LED2: TOTX1950A_F_; TOTX1950AF; Mouser Part Number 757-TOTX1950AF
Q1, Q2, Q3, Q4, Q5: BSS138; SOT-23
R1, R2: 5.6k; R_0603_1608Metric_Pad0.98x0.95mm_HandSolder
R3: 10k; R_0805_2012Metric_Pad1.20x1.40mm_HandSolder

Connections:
+3.3V: J1.3, Q1.2 (S), Q2.2 (S), Q3.2 (S)
/IN 1: J1.4, Q4.1 (G)
/IN 2: J1.5, Q5.1 (G)
/OUT 1: J1.8, Q1.3 (D)
/OUT 2: J1.7, Q2.3 (D)
/OUT 3: J1.6, Q3.3 (D)
GND: C1.2, C2.2, C3.2, C4.1, C5.1, H1.1, H2.1, IC1.2 (GND1), IC1.4 (GND2), IC2.2 (GND1), IC2.4 (GND2), IC3.2 (GND1), IC3.4 (GND2), J1.1, LED1.1 (GND), LED2.1 (GND), R3.2
unnamed: C1.1, IC1.3 (VCC), L1.2
unnamed: C2.1, IC2.3 (VCC), L2.2
unnamed: C3.1, IC3.3 (VCC), L3.2
unnamed: D1.1 (K), R3.1
unnamed: IC1.1 (OUTPUT), Q1.1 (G)
unnamed: IC2.1 (OUTPUT), Q2.1 (G)
unnamed: IC3.1 (OUTPUT), Q3.1 (G)
unnamed: LED1.2 (_CURRENT_LIMITING_RESISTOR_OF_LED), R1.2
unnamed: LED1.4 (INPUT), Q4.3 (D)
unnamed: LED2.2 (_CURRENT_LIMITING_RESISTOR_OF_LED), R2.2
unnamed: LED2.4 (INPUT), Q5.3 (D)
VCC: C4.2, C5.2, D1.2 (A), J1.2, L1.1, L2.1, L3.1, LED1.3 (VCC), LED2.3 (VCC), Q4.2 (S), Q5.2 (S), R1.1, R2.1

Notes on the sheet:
Transmitter
Version 1
Max Chastain Trasmitter Unit For use with CHAMELEON project

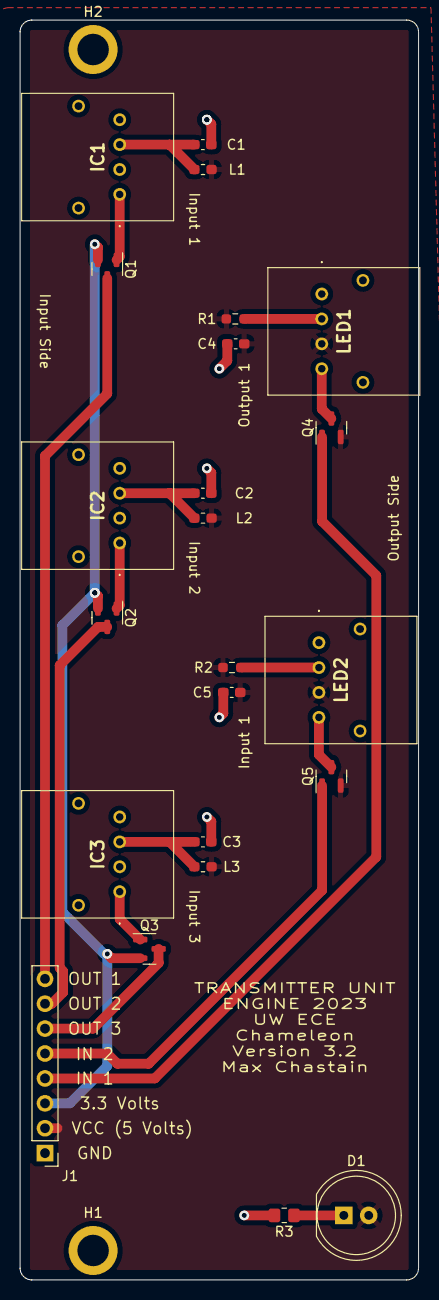
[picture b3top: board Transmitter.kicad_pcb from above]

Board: 2 copper layers, 40.6 x 128.5 mm, 25 parts (0 on the bottom side), 19 nets.

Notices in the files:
parts and their libraries:
Copyright 2021 Accelerated Designs. All rights reserved.
